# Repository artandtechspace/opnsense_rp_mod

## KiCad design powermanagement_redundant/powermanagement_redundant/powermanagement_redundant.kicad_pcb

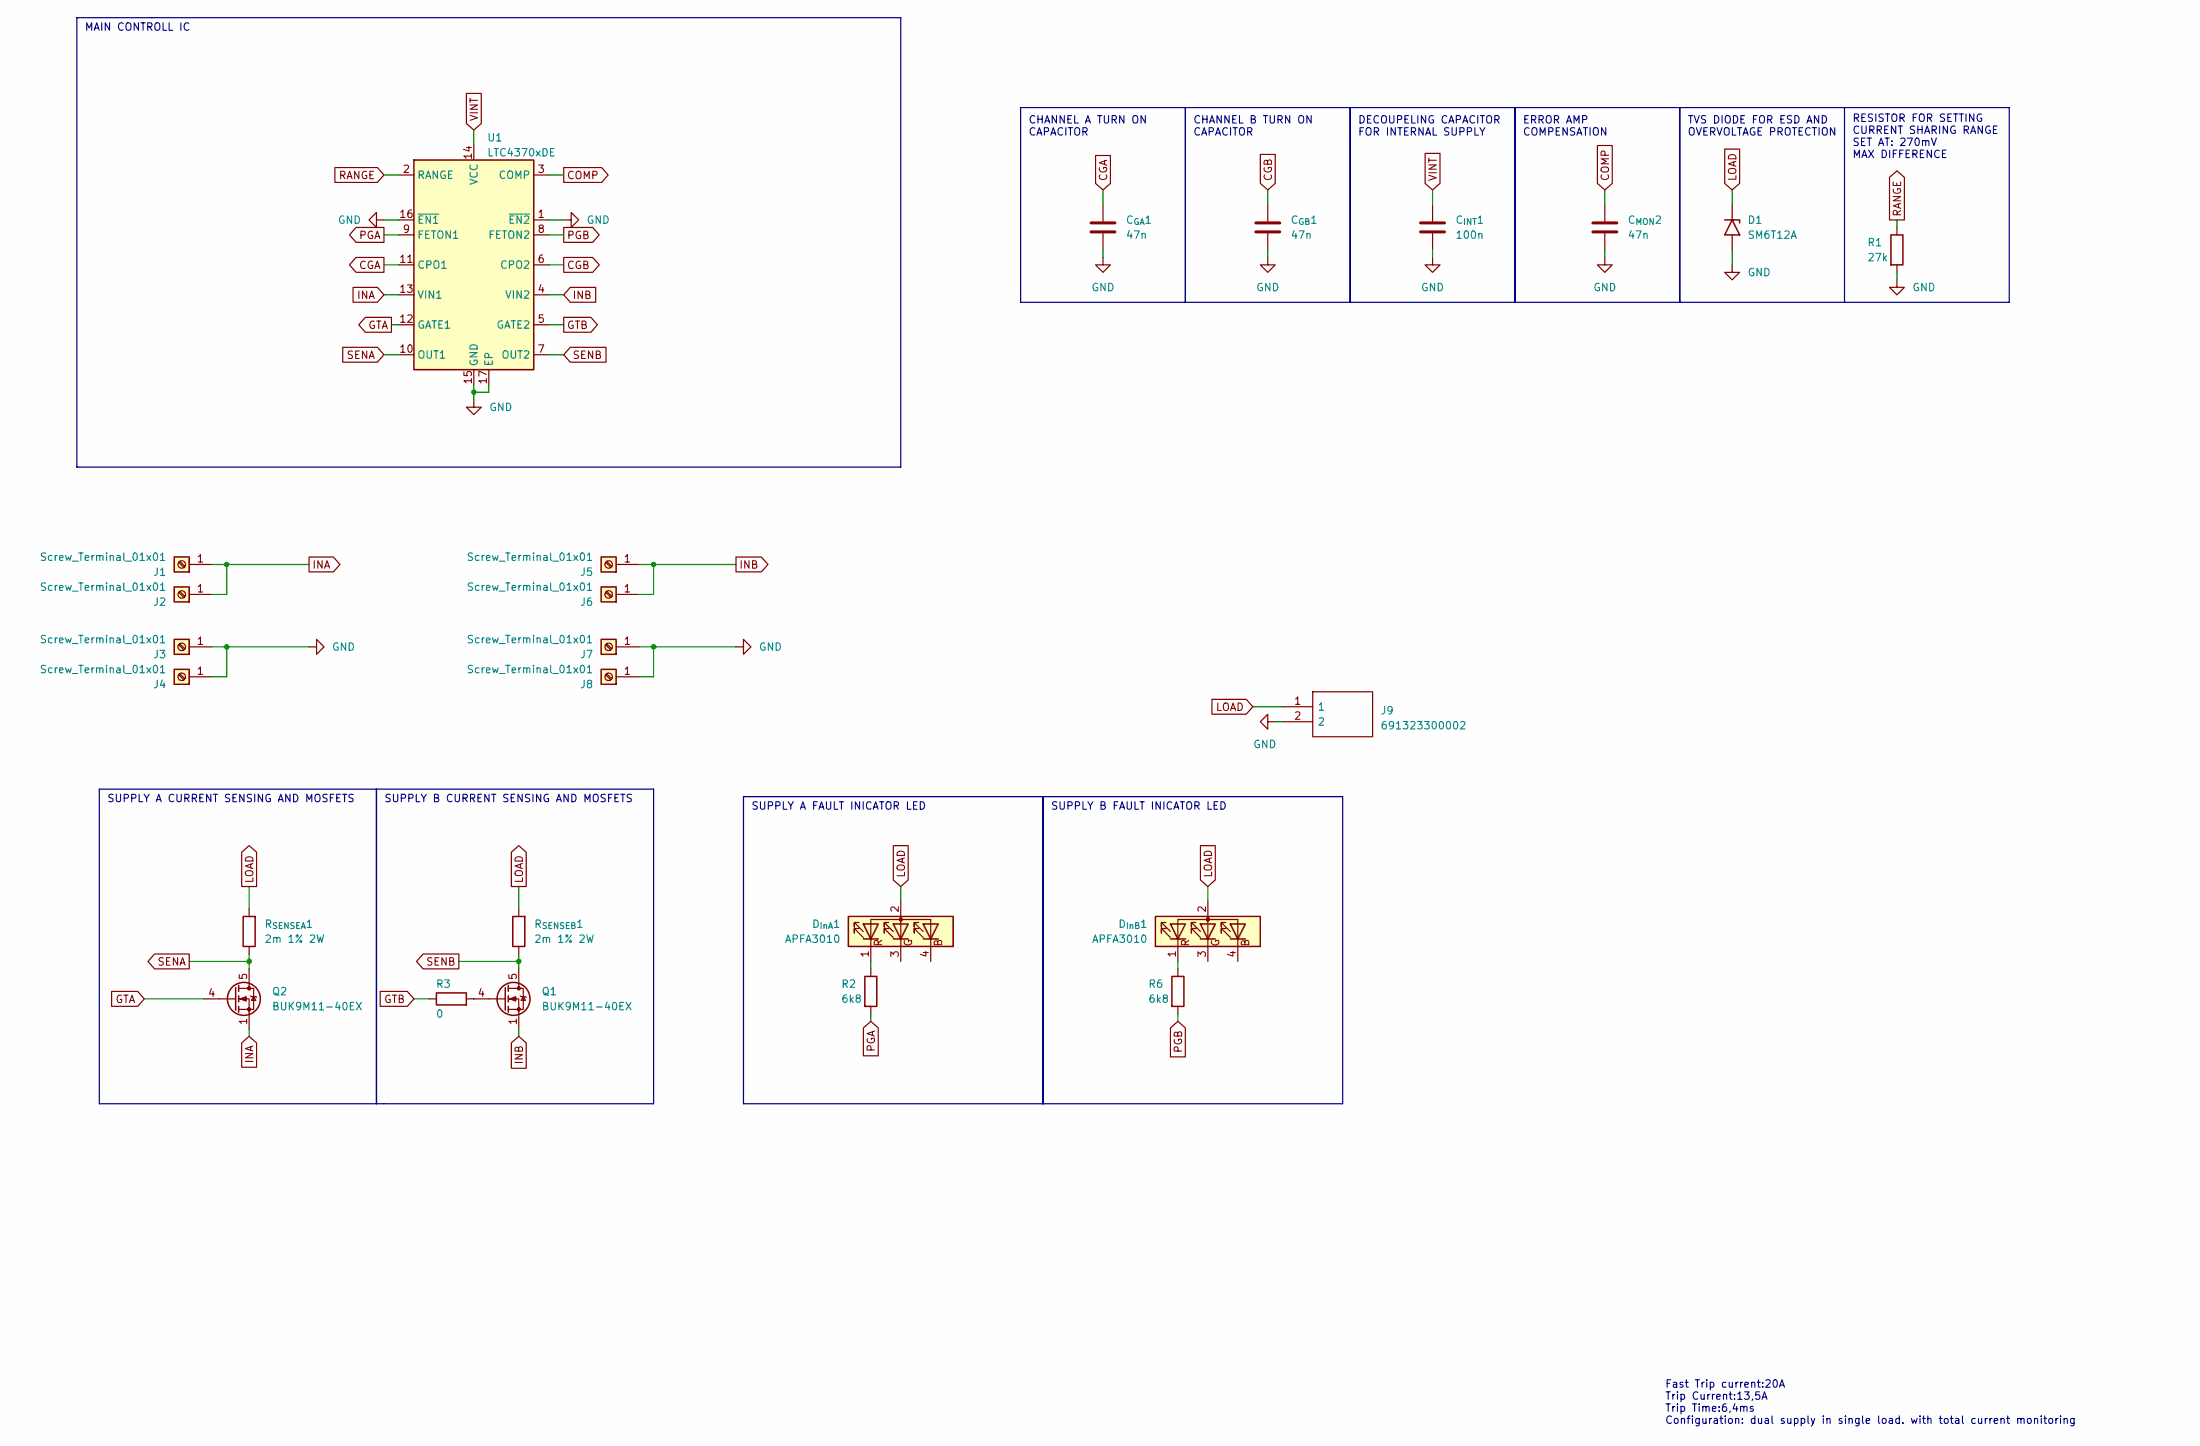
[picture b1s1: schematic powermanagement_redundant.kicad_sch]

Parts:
C_{GA}1: 47n; C_0805_2012Metric
C_{GB}1: 47n; C_0805_2012Metric
C_{INT}1: 100n; C_0805_2012Metric
C_{MON}2: 47n; C_0805_2012Metric
D1: SM6T12A; D_SMB
D_{InA}1: APFA3010; LED_Kingbright_APFA3010_3x1.5mm_Horizontal
D_{InB}1: APFA3010; LED_Kingbright_APFA3010_3x1.5mm_Horizontal
J1, J2, J3, J4, J5, J6, J7, J8: Screw_Terminal_01x01; MountingHole_3.5mm_Pad
J9: 691323300002; Mouser Part Number 710-691323300002
Q1, Q2: BUK9M11-40EX; LFPAK33
R1: 27k; R_0805_2012Metric
R2, R6: 6k8; R_0805_2012Metric
R3: 0; R_0805_2012Metric
R_{SENSEA}1: 2m 1% 2W; R_0612_1632Metric
R_{SENSEB}1: 2m 1% 2W; R_0612_1632Metric
U1: LTC4370xDE; DFN-16-1EP_3x4mm_P0.45mm_EP1.7x3.3mm

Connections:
CGA: C_{GA}1.1, U1.11 (CPO1)
CGB: C_{GB}1.1, U1.6 (CPO2)
COMP: C_{MON}2.1, U1.3 (COMP)
GND: C_{GA}1.2, C_{GB}1.2, C_{INT}1.2, C_{MON}2.2, D1.2 (A2), J3.1, J4.1, J7.1, J8.1, J9.2, R1.2, U1.1 (~EN2), U1.15 (GND), U1.16 (~EN1), U1.17 (EP)
GTA: Q2.4 (G), U1.12 (GATE1)
GTB: R3.1, U1.5 (GATE2)
INA: J1.1, J2.1, Q2.1 (S), Q2.2 (S), Q2.3 (S), U1.13 (VIN1)
INB: J5.1, J6.1, Q1.1 (S), Q1.2 (S), Q1.3 (S), U1.4 (VIN2)
LOAD: D1.1 (A1), D_{InA}1.2 (A), D_{InB}1.2 (A), J9.1, R_{SENSEA}1.2, R_{SENSEB}1.2
unnamed: D_{InA}1.1 (R), R2.1
unnamed: D_{InB}1.1 (R), R6.1
unnamed: Q1.4 (G), R3.2
PGA: R2.2, U1.9 (FETON1)
PGB: R6.2, U1.8 (FETON2)
RANGE: R1.1, U1.2 (RANGE)
SENA: Q2.5 (D), R_{SENSEA}1.1, U1.10 (OUT1)
SENB: Q1.5 (D), R_{SENSEB}1.1, U1.7 (OUT2)
VINT: C_{INT}1.1, U1.14 (VCC)

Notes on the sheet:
CHANNEL A TURN ON CAPACITOR
SUPPLY B CURRENT SENSING AND MOSFETS
MAIN CONTROLL IC
RESISTOR FOR SETTING CURRENT SHARING RANGE SET AT: 270mV MAX DIFFERENCE
SUPPLY A FAULT INICATOR LED
ERROR AMP COMPENSATION
SUPPLY A CURRENT SENSING AND MOSFETS
TVS DIODE FOR ESD AND OVERVOLTAGE PROTECTION
Fast Trip current:20A Trip Current:13,5A Trip Time:6,4ms Configuration: dual supply in single load. with total current monitoring
CHANNEL B TURN ON CAPACITOR
DECOUPELING CAPACITOR FOR INTERNAL SUPPLY
SUPPLY B FAULT INICATOR LED

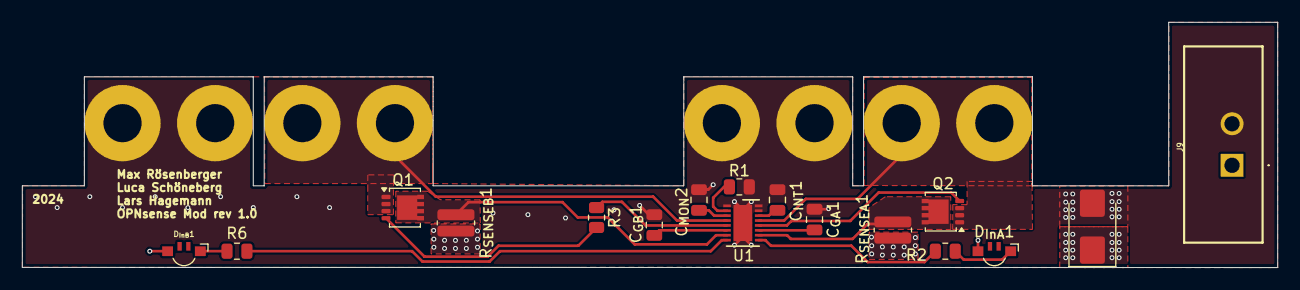
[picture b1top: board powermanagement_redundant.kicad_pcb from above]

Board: 2 copper layers, 115.2 x 22.5 mm, 25 parts (0 on the bottom side), 18 nets.

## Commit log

2023-02-05 change
2023-02-10 Neue Bibliothek
    Neuste Version
2023-02-10 Bauteileplatzierung Fertig!
    Alle Bauteile sind jetzt alle platziert. Werte die bereits Bekannt sind hab ich auch eingetragen. Berechnung der Bauteile erfolgt demnächst.
2023-02-13 Komponenten finalisiert und ein wenig aufgeräumt
    Den Schaltplan weitesgehen finalisiert.
    PG und FLT LEDS hinzugefügt.
    Fault clear Button hinzugefügt.
    Wiederstände fürs current sensing berechnet.
    Schaltplan aufgeräumt.
    Soft turn on schaltung hinzugefügt
2023-02-14 Paar fehler gefixed und Footprints zugeordnet
    Im Schaltplan noch ein paar fehler gefixed, Footprints zugeordnet und Komponenten rausgesucht.
2023-02-14 PCB angefangen
    PCB halt angefangen
2023-02-15 Alle komponenten auf der Platine Platziert
    Alles passt iwie ist aber knapp.
2023-02-15 kicad 7
2023-02-15 add PCB and make it for Aisler work
2023-02-15 add text
2023-02-15 update some text
2023-02-16 rev.01
2023-02-21 last commit rev 1.0
2023-03-02 upgrade mosfet footprint, change some values
2023-04-19 Mosfets getauscht.
    Die Mosfets hab ich gegen CSD87313DMS getauscht. Im gleichen Schritt hab ich die Pads überarbeitet. Die haben jetzt einen vollständigen Übergangauf zum Backlayer.
2023-04-19 Verschraub-Punkte verändert
2023-05-01 Ein paar dinge verändert
2023-12-28 Kompletto auf anderes ic umgebaut
2023-12-29 silkscreen changes
2024-10-06 N-Channel MOSFET falsche Orientierung
    Die Orientierung des N-MOSFET ist geändert. Vor der Fertigung muss noch auf der PCB die Versions Nummer geändert werden.
2024-10-09 fix some issues for Aisler Order
2024-12-21 Bom Erstellt
